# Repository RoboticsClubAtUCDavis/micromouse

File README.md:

# micromouse

## Contributing

`dev` is the main development branch of the project. `dev` is a protected branch set to reject any commits that have not passed the automated checks performed by *Travis CI*. In order to push to `dev` you must first push a new branch with your changes to GitHub. The automated tests will run within a minute or two and if they pass you will be able to push your commits to `dev`.

#### The recommended workflow for making new features/changes is:
  1. Checkout `dev` and pull the latest changes from GitHub
    - `git checkout dev`
    - `git pull origin dev`
  2. Make a new branch for your changes
   - `git checkout -b <branch-name>`
  3. Make your changes and commits (There are many commands/options to accomplish this, these are just a few)
     - See what changes you made:
      - `git status`  - Shows the modified files
      - `git diff [<file-name>]` - Shows the modified lines
     - Stage the changes (Choose what changes will be part of the commit)
      - `git add <file-name>` - Add a specific file or pattern
      - `git add -p` - Interactively choose chunks of code to add (My favorite)
      - `git add .` - Add all changes (Use sparingly)
     - Make the commit
      - `git commit -m "<commit-message>"` - When the commit message is short
      - `git commit` - Will open a text editor to enter longer commit messages
  4. Get any new changes from `dev` (It is a good idea to do this throughout the development of your feature as well.)
    - `git pull origin dev`
  5. Push your branch to GitHub
    - `git push origin <branch-name>`
  6. Wait to see if the checks passed. If they pass, create a pull request on GitHub.
    - `GitHub` > `Pull requests` >  `New pull request` > `compare: <branch-name>` > `Create pull request` > Fill in the description > `Create pull request`
    
### Code Formatting
Keeping a consistent code format is important and reduces the occurrences of merge conflicts.

To keep a consistent style on all platforms we are using *Clang-format*.

#### If you are using Visual Studio, here is how to set it up:
- Go `To Tools` > `Extensions and Updates`
- Click on `Online` and in the top right search "clangformat"
- Click `Download`, `Install` and then `Restart Now`

##### To use Clang-format:
- With a file open, go to `Tools` and select either `Clang Format Selection (Ctrl-R, Ctrl-F)` or `Clang Format Document  (Ctrl-R, Ctrl-D)`

##### Notes:
- Do not use `Clang Format Document` if the file you are working in was not previously formatted. This will create a lot of unnecessary noise in the commits. However all existing code is now formatted so this should not be an issue. 
- It is best to either:
  - Format before making each commit 
  - Or wait until you are done adding code and have committed all your changes. Then format all your changes in a single commit at the end.
- We may reject your code if it is not properly formatted.

## Setting up the simulation

#### If you are using Visual Studio:
1. Download the **32-bit** version of [SFML 2.4.2](http://www.sfml-dev.org/download/sfml/2.4.2/).
2. Extract the files.
3. Place the extracted folder `SFML-2.4.2` at the root of the project folder.
4. Copy all DLL files in `\SFML-2.4.2\bin` to `\Simulation`
5. In Studio right-click the `Simulation` project and select `Set as StartUp Project`.
6. Build and run the project

#### On Linux:
1. Install SFML (for example, `sudo pacman -S sfml` on Arch Linux; `sudo apt-get install sfml` on Ubuntu)
2. Install `scons` and `gcc` the same way, if you do not already have them
3. Build with `scons`
4. Run with `./simulate`

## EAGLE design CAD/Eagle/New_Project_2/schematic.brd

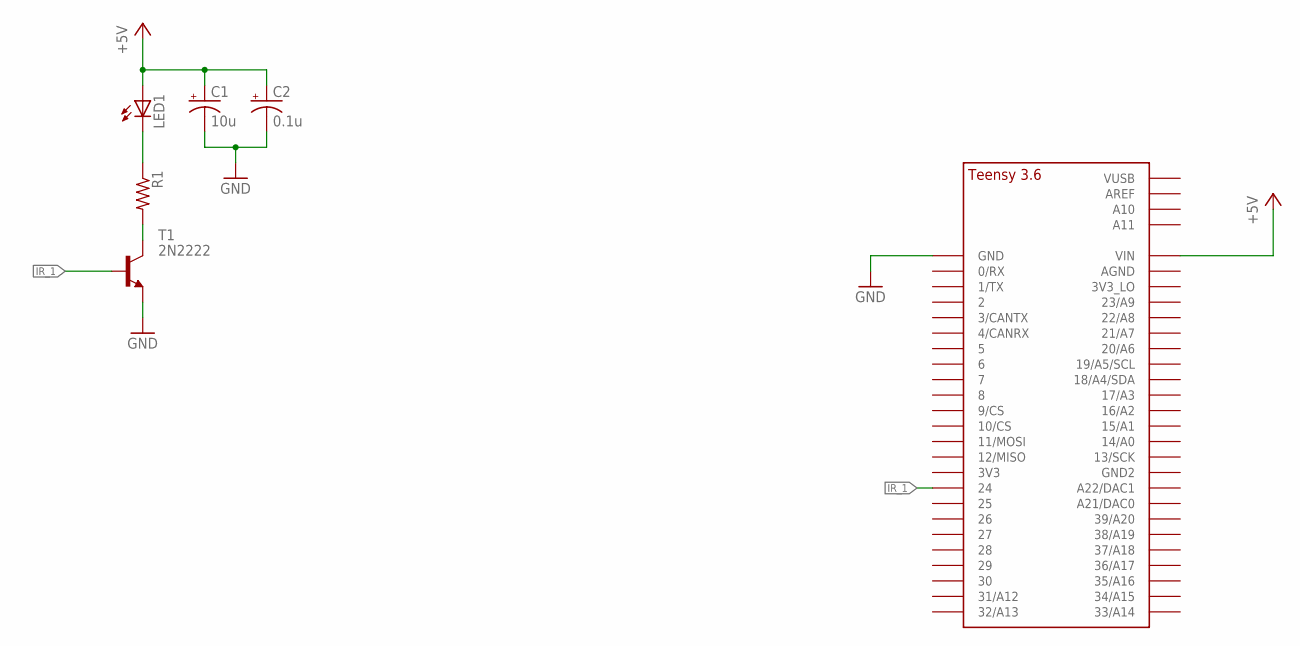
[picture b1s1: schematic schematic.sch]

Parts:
C1: 10u; E3,5-8
C2: 0.1u; E1,8-4
LED1: LED5MM
R1: R-US_0204/7; 0204/7
T1: 2N2222; TO92-EBC-OVAL
U$1: TEENSY_3.5/3.6_BASIC

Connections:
+5V: C1.+, C2.+, LED1.A, U$1.VIN
GND: C1.-, C2.-, T1.E, U$1.GND
IR_1: T1.B, U$1.24
unnamed: R1.2, T1.C
unnamed: LED1.K (C), R1.1

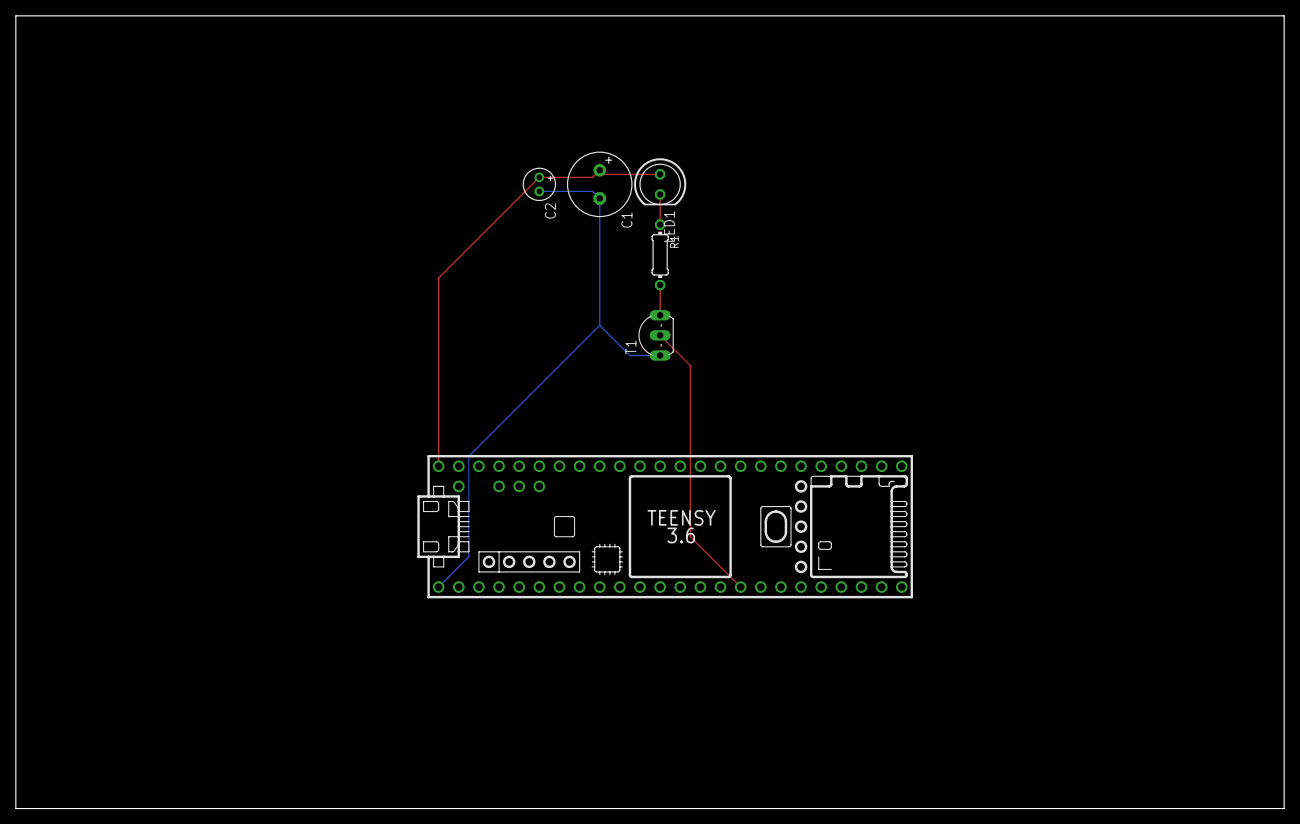
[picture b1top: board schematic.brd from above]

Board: 2 copper layers, 160.0 x 100.0 mm, 6 parts (0 on the bottom side), 5 nets.

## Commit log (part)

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2017-02-23 Update Makefile
2017-02-25 Initial simulation code (doesn't display anything yet)
2017-02-25 Draw border in simulator
2017-02-25 Correct loop condition
2017-02-25 Have Makefile build with debugging symbols
2017-02-25 Correction (hopefully)
2017-02-25 Make Simulator a subclass of RenderWindow
2017-02-25 Allow window resize; generate cell size to match window size
2017-02-25 Correction to resizing
2017-02-25 Make members that do not need to be public private
2017-02-25 Add .travis.yml
2017-02-25 Try adding PPA to .travis.yml to get up to date sfml
2017-02-25 -y to apt-get
2017-02-26 Make Coordinate constructor protected
2017-02-26 Add Simulation project to VS
2017-02-26 Revert "Add Simulation project to VS"
    This reverts commit 0d9e8bb8d86124bd14adee41dfeec50dda4f9b5d.
2017-02-27 Fix CellCoordinate->NodeCoordinate conversion
2017-02-27 Add implicit conversion operator from CellCoordinate->NodeCoordinate
2017-02-27 Reorder the Direction enum and add NONE value
2017-02-27 Add default constructor for Maze
2017-02-27 Implement findPath and helper functions
2017-02-27 Update gitignore for SFML
2017-02-27 Update maze initialization
2017-02-27 Link Path.o into simulator
2017-02-28 Fix findPath not checking for walls (kind of important)
2017-02-28 Correction to simulator
    Row and col were swapped
2017-02-28 Make wall=true default for setWall
2017-02-28 Favor paths with fewer turns
2017-02-28 Fix turn calculation
2017-03-02 Defined overloaded operator+ for coorinates, replaced usage with operating loading in Maze::setWall(CellCoordinate pos, Direction, dir) and Maze::isWall(CellCoordinate pos, Direction dir) closes#12
2017-03-02 Fixed coordinates
2017-03-02 Correct Maze::setWall
2017-03-02 Added overload operators for Direction Vector in coordinate file
2017-03-02 Add load maze from file
2017-03-02 Add return statement to Maze::isWall
2017-03-02 Clean up loadMazeFromFile
2017-03-02 Correct cell calculations in simulator
2017-03-02 Set maze border on reset() Also changed the drawCell function, appears that the coordinate system starts at the lower right corner.
2017-03-02 Fix grabbing the newlines when loading maze from file
2017-03-02 Remove Node::setScores(...)
2017-03-02 Created empty classes for motor, encoder, rangefinder, led, and hardware
2017-03-02 Remove 64bit build from Visual Studio
2017-03-02 Fixed class definition and class function for motor, encoder, rangefinder, led, and hardware
2017-03-02 Remove now-unneeded drawBorder() method
2017-03-02 Correct warning
2017-03-02 Try again to fix travis
2017-03-02 Travis again
2017-03-02 Add dependency to .travis.yml
2017-03-02 Travis fix
2017-03-02 Cache sfml in travis
2017-03-02 Run clang-formate on simulator
2017-03-02 Update gitignore for dll
2017-03-02 Add Catch unit-testing and Test project in VS
2017-03-02 Add sample unit test for Direction
2017-03-02 Add check target to Makefile for running tests
2017-03-03 Pathfind from end to start
2017-03-03 Run clang format on additions
2017-03-03 Include <string>
2017-03-03 Add missing break statements
2017-03-03 Draw path (currently crashing in pathfinder)
2017-03-03 Fix bounds on for-loops for Maze::resetNodePathData
2017-03-03 Fix throwing on 180deg turn in Maze::calculateMovementCost
2017-03-03 Update simulation to test path finding
2017-03-03 Path finding seems to be working correctly
2017-03-03 Make path green
2017-03-03 Make getNode() check bounds (throwing exception) and return reference
2017-03-03 Use getNode() in isWall() and setWall()
2017-03-03 Correct coordinate/vector addition overloads
2017-03-03 SConstruct correction
2017-03-03 Fix pathfinding
    I forgot to give a comparitor to the openNodes set. However set can only be weakly sorted because of their underlying implementation so instead I used a vector. We may want to come up with a more opt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
2017-03-03 Remove <set> include
2017-03-03 Fix scoping
2017-03-03 Update .clang-format
2017-03-03 Create MazeDrawable class, and move some logic to it
2017-03-03 Inherit sf::Transformable, and use it to implement margin
2017-03-03 Use sf::Transformable to set scale
2017-03-03 Run clang-format on simulate.cpp
2017-03-03 Update Clang-format
2017-03-03 Format Encoder, Hardware, Led, Motor, and RangeFinder
2017-03-03 Format Coordinate and Direction
2017-03-03 Format Main.cpp
2017-03-04 maze_size no longer needs to be member
2017-03-04 Remove maze_size member
2017-03-04 Slight correction of margins
2017-03-04 Slight simplification to nodeVector()
2017-03-04 Slight refactoring to simulator
2017-03-04 scons changes
2017-03-04 Call resetPathData() in Node constructor
2017-03-04 Have simulator calculate new path on return keypress, not timer
2017-03-04 Fixed class definition and class function for motor
2017-03-04 Add #pragma once to Node.h
2017-03-04 Format Motor.h
2017-03-04 Test push rejection
2017-03-04 Revert "Test push rejection"
    This reverts commit 5c9ebc713844d5846c5a65fcf0b1cf9dc3b6a5e4.
2017-03-05 Linux build instructions
2017-03-05 Fix cache issue causing file in wrong directory
2017-03-05 maze generation using backtrack algorithm
2017-03-05 Goal now has only one entrance
2017-03-06 Fix paths constructed with extra step at end
2017-03-06 Add function to invert Directions and DirectionVectors
2017-03-06 Fix findPath not correctly handling the 'facing' parameter
2017-03-06 Forgot formatting
2017-03-06 Add initial definition of Hardware class
2017-03-06 Keybindings for simulator
2017-03-06 Update Mouse interface
2017-03-07 Properly setup project dependencies and settings in VS
2017-03-09 Add default ctors for NodeCoordinate and CellCoordinate
2017-03-09 Create empty functions for Mouse
2017-03-09 Implement trivial Mouse functions
2017-03-09 Implimented Led class
2017-03-09 Format Led files
2017-03-09 Added changes to Led files
2017-03-09 Changes to Led files
2017-03-09 Add ArduinoSpoof.h
2017-03-09 Add missing spoof functions
2017-03-09 Fix unused parameters
2017-03-10 Incomplete teensy build support, with scons
2017-03-10 move ArduinoSpoof.h
2017-03-10 Changes to brightness in led.cpp
2017-03-10 Changes to brightness function in led.cpp
2017-03-10 Remove iostream
2017-03-10 Update gitignore
2017-03-10 Fix and rename ArduinoSpoof.h -> Arduiono.h
2017-03-10 Remove Main.cpp
2017-03-10 Compiles on Teensy
2017-03-10 Set functions as static so they are only defined once
2017-03-10 Move to cpp and remove srandom
2017-03-11 Created and Implimented LedRGB class
2017-03-11 Added basic tests for coordinates
2017-03-11 Added basic tests for coordinates -removed null tests
2017-03-11 Changes to led.cpp and redoing git
2017-03-12 Added remaining tests Also updated the vs solution to include the new test file
2017-03-12 Move Arduino.*
2017-03-12 Move simulate.cpp to Simulate director
2017-03-12 Update VS project files
2017-03-12 Revert .gitignore
2017-03-12 Change SConstruct for moved filed; use glob instead of explicit names
2017-03-12 Fix build errors
2017-03-12 Changes to ledRGB class, replaced arduino functions
2017-03-12 Enable throws on pc builds
2017-03-12 Change back-slash to forward-slash
2017-03-12 Add initial interface for RangeFinder
2017-03-12 Add IRSensor and UltraSonicSensor that inherit from RangeFinder
2017-03-12 Use ArduinoSpoof in RangeFinder
2017-03-12 Setup RangeFinders in Hardware
2017-03-12 Implement some uses of RangeFinders within Hardware
2017-03-12 Update simulator to use Mouse object
2017-03-12 Move IRSensor
2017-03-12 Change for-loops
2017-03-12 Reorder initializor list
2017-03-12 Disable emails from Travis
2017-03-12 Use range-based for loop
2017-03-12 Make Simulate friend of Mouse
2017-03-12 Remove maze member from Simulator (just use mouse.maze)
2017-03-12 Add comment
2017-03-13 Fixed turnOff function and made changes to setRGB and setBrightness function in ledRGB class
2017-03-14 Changed brightness to float, set default values for colors and brightness. Changed setRGB and setBrightness functions
2017-03-14 Changed brightness to double, Made red, blue, green leds privates
2017-03-14 Set default brightness values in LedRGB class
2017-03-14 Add mock teensy object
2017-03-14 Added and implimented blink function
2017-03-14 Make everything in Teensy public
2017-03-14 Fix ambiguous call
2017-03-14 Make teensy extern
2017-03-14 Add Test-Led.cpp to project
2017-03-14 Add units test for Led
2017-03-15 Implimented blink function
2017-03-16 Inherritance for LedRGB
2017-03-16 Move LedRGB files
2017-03-16 Add newline to prints
2017-03-16 Remove memory file from repo
2017-03-17 Change findPath to take NodeCoordinates
2017-03-17 Add settings to render window
2017-03-17 Add thread for simulation
2017-03-17 Add temp runMaze for testing
2017-03-17 Remove unused var
2017-03-17 Remove c++14 literal feature
2017-03-17 move implementation to cpp file (except templates)
2017-03-17 Compile on Teensy
2017-03-17 Add NEAT Visualizer to simulation
    https://sourceforge.net/projects/neatvisualizers/
    It currently evolves an XOR network as provided in the example.
2017-03-18 Have simulator set its own antialias step
2017-03-18 Maze mouse thread owned by Simulator
2017-03-20 Extend findPath
    findPath now supports multiple end points and an option to limit search to explored nodes only.
    When multiple end points are give the path to the closest is generated.
2017-03-20 Fix heuristic for non-diagonals
2017-03-20 Add new maze files
2017-03-20 Add header for simulation globals
2017-03-20 Fix compile on Teensy
2017-03-20 Make Coordinate const correct
2017-03-20 Add more colors to simulation
2017-03-20 Clean/reorganize up Maze
2017-03-20 Add getter and setters for explored
2017-03-20 Update simulation to use mapping and be thread safe
2017-03-20 Rename test.maze
2017-03-21 Fix states swapped
2017-03-21 Change simulation speed at runtime
2017-03-29 Add PIDController class
2017-03-29 Add PIDControllers to Hardware
2017-04-05 Remove unimplement default ctor
2017-04-05 Make data members const
2017-04-24 Display walls that have not yet been found, but grayed out
2017-04-24 Add color gradient to pathfind visualization
2017-04-25 Remove unused variables
2017-04-25 Add <cmath> include
    This was failing to compile on my computer.
2017-04-29 First shot at moveForward
2017-04-29 Finish Hardware::moveForward
2017-04-29 Update things after rebase
2017-04-30 Add calibration routine for IRSensor
2017-04-30 Refactor IRSensor::readSensor
2017-04-30 Replace manual pin manipulation with LED
2017-05-01 Implement angleDiff() (#21)
2017-05-01 Initial implementation of Mouse::followPath() and Mouse::move() (#84)
2017-05-02 Draw a vector field for pathfinding in sim
2017-05-03 Add testing modes for hardware actions
2017-05-04 Add BFS mapping strategy
2017-05-05 Make Maze::generate static. Minor refactor
2017-05-05 Make some maze functons const
2017-05-05 Minor changes
2017-05-05 Add returning to start to mapping cost
2017-05-05 Fix warnings
2017-05-07 Refactor iteration over enums
2017-05-07 Add more Maze helper functions
2017-05-07 Add DFS mapping strategy
2017-05-07 Fix accidentally unused parameters
2017-05-07 Fix implicit conversion Direction->Coordinat
2017-05-07 Add a mapping ranking function
2017-05-12 Set pin values and use them in the ctors
2017-05-12 Fix logic error in mock Teensy
2017-05-12 Disable simulation related code
2017-05-13 Fixes after testing on Teensy
2017-05-13 Motor direction
2017-05-17 Fix pins
2017-05-17 Work on tuning movement
2017-07-07 Add component tests to the solution
2017-07-26 Remove literal expressions
2017-08-06 Revert "Remove literal expressions"
    This reverts commit 217a6fb57dc626faf3d4e10abac45e0ddc4f463f.
2017-08-06 Fix max input
2017-08-11 Change file name in VS project files
2017-08-11 Add misc files to vs solution
2017-08-12 Fix project dependencies
2017-08-12 Format code
2017-08-13 Add additional hardware constants
2017-08-13 Modify speedPID tuning a bit
2017-08-13 Enable second motor, disable IR distance correction
2017-08-13 Change motors to use enable/phase
2017-08-13 Disable right motor during testing
2017-08-13 Update scons build scripts
2017-08-13 Second attempt: Add scons test alias
2017-08-13 Update LED tests
2017-08-13 Fix all compiler warnings
